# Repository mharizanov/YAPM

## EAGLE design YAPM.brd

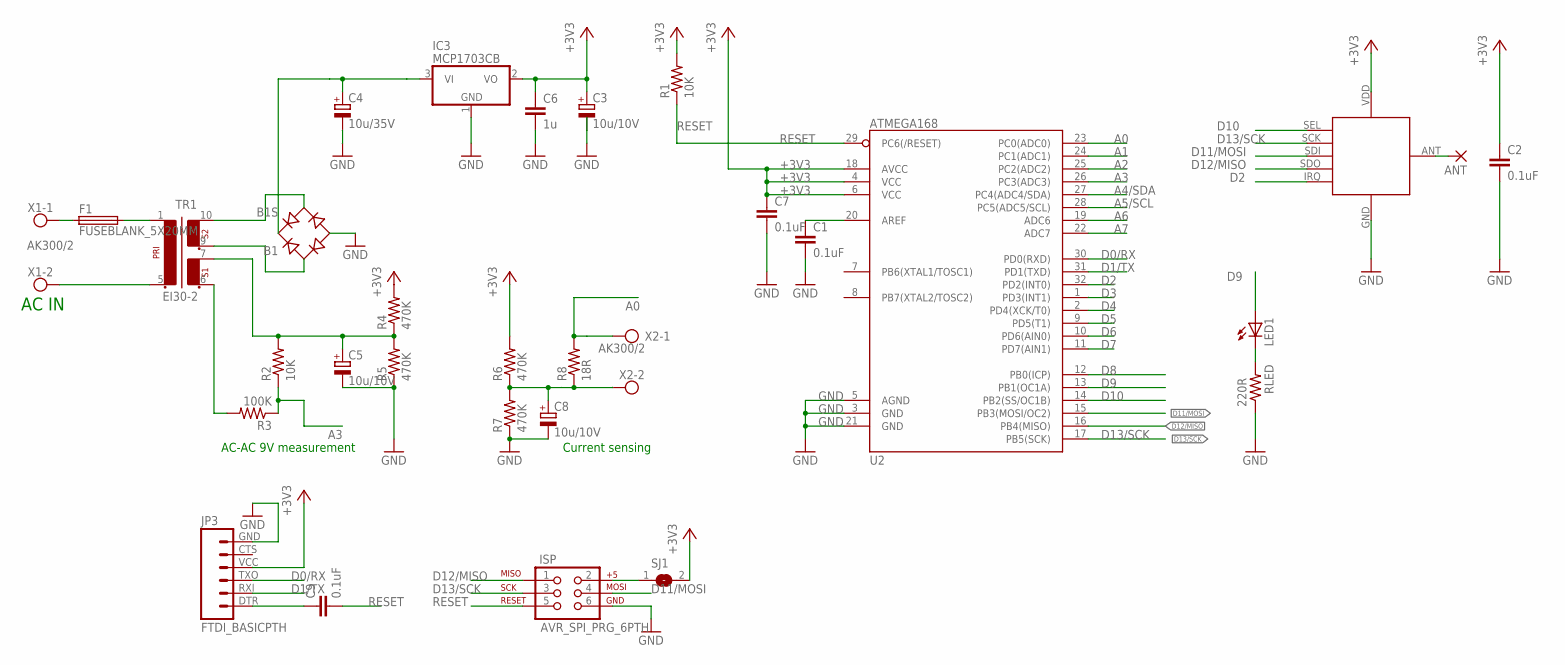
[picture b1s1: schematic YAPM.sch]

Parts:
ANT: 1,6/0,8
B1: B1S; MBS
C1, C2, C7, C9: 0.1uF; C0603
C3, C5, C8: 10u/10V; SMC_A
C4: 10u/35V; SMC_C
C6: 1u; C0603K
F1: FUSEBLANK_5X20MM; FUSE_HOLDER_5X20MM
IC3: MCP1703CB; SOT23
ISP: AVR_SPI_PRG_6PTH; 2X3
JP3: FTDI_BASICPTH; FTDI_BASIC
LED1: LEDSML0603; SML0603
R1, R2: 10K; R0603
R3: 100K; R0603
R4, R5, R6, R7: 470K; R0603
R8: 18R; R0603
RFM12B1: RFM12B_MINPADS; RFM12B-MINPADS
RLED: 220R; R0603
SJ1: SJ
TR1: EI30-2
U2: ATMEGA168; TQFP32-08
X1, X2: AK300/2

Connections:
+3V3: C2.1, C3.+, C6.1, C7.1, IC3.2 (VO), JP3.VCC (4), R1.2, R4.2, R6.2, RFM12B1.VDD, SJ1.2, U2.4 (VCC), U2.6 (VCC), U2.18 (AVCC)
+5V: ISP.2, SJ1.1
A0: R8.2, U2.23 (PC0(ADC0)), X2.1
A1: U2.24 (PC1(ADC1))
A2: U2.25 (PC2(ADC2))
A3: R2.1, R3.1, U2.26 (PC3(ADC3))
A4/SDA: U2.27 (PC4(ADC4/SDA))
A5/SCL: U2.28 (PC5(ADC5/SCL))
A6: U2.19 (ADC6)
A7: U2.22 (ADC7)
D0/RX: JP3.TXO (3), U2.30 (PD0(RXD))
D1/TX: JP3.RXI (2), U2.31 (PD1(TXD))
D2: RFM12B1.IRQ, U2.32 (PD2(INT0))
D3: U2.1 (PD3(INT1))
D4: U2.2 (PD4(XCK/T0))
D5: U2.9 (PD5(T1))
D6: U2.10 (PD6(AIN0))
D7: U2.11 (PD7(AIN1))
D8: U2.12 (PB0(ICP))
D9: LED1.A, U2.13 (PB1(OC1A))
D10: RFM12B1.SEL, U2.14 (PB2(SS/OC1B))
D11/MOSI: ISP.4, RFM12B1.SDI (SDI/MOSI), U2.15 (PB3(MOSI/OC2))
D12/MISO: ISP.1, RFM12B1.SDO (SDO/MISO), U2.16 (PB4(MISO))
D13/SCK: ISP.3, RFM12B1.SCK, U2.17 (PB5(SCK))
GND: B1.-, C1.2, C2.2, C3.-, C4.-, C5.-, C6.2, C7.2, C8.-, IC3.1 (GND), ISP.6, JP3.GND (6), R5.1, R7.1, RFM12B1.GND, RLED.1, U2.3 (GND), U2.5 (AGND), U2.21 (GND)
unnamed: F1.2, TR1.1
unnamed: F1.1, X1.1
unnamed: B1.AC2, TR1.10 (6)
unnamed: B1.AC1, TR1.9 (5)
unnamed: B1.+, C4.+, IC3.3 (VI)
unnamed: C1.1, U2.20 (AREF)
unnamed: ANT.1, RFM12B1.ANT
unnamed: LED1.C, RLED.2
unnamed: C8.+, R6.1, R7.2, R8.1, X2.2
unnamed: C9.1, JP3.DTR (1)
unnamed: C5.+, R2.2, R4.1, R5.2, TR1.7 (4)
unnamed: R3.2, TR1.6 (3)
unnamed: TR1.5 (2), X1.2
RESET: C9.2, ISP.5, R1.1, U2.29 (PC6(/RESET))

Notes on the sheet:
AC IN
AC-AC 9V measurement
Current sensing

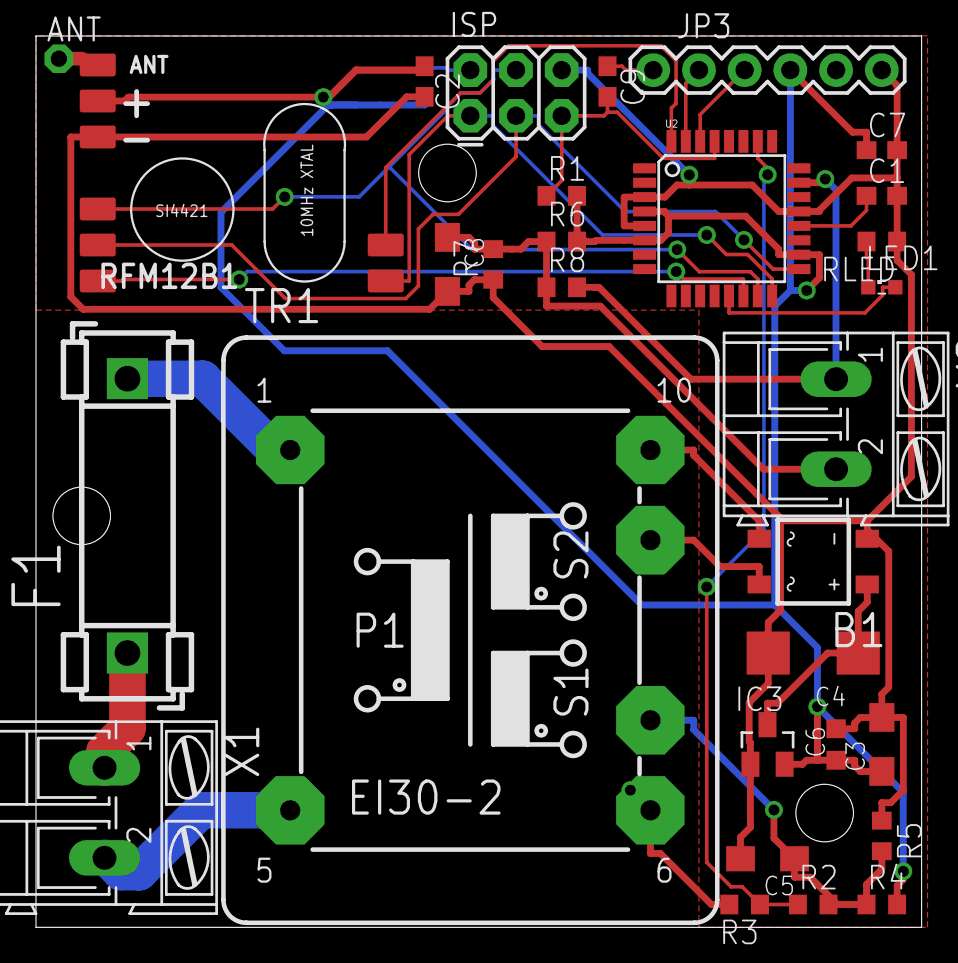
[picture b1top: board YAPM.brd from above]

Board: 2 copper layers, 49.2 x 49.5 mm, 31 parts (1 on the bottom side), 27 nets.

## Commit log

2014-01-16 Initial version
2014-01-18 software updates
2014-12-12 Updated Sketch
